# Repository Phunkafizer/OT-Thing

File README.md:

# OTthing

**A compact WiFi <-> OpenTherm (master & slave) interface**

## Project homepage

https://www.seegel-systeme.de/2025/01/05/ot-thing-das-universelle-wifi-opentherm-interface/

*OTthing board*

*OTthing wiring*

*OTthing web interface*

*Home Assistant integration*

## Overview

OTthing is a versatile OpenTherm gateway that connects your heating system to the Internet via WiFi. It acts as an OpenTherm master (controlling your boiler) and/or slave (integrating with room thermostats), providing real-time monitoring and control through a modern web interface and Home Assistant integration.

### Key Features

* **Dual OpenTherm Modes**: Operate as both an OpenTherm master and a slave simultaneously
* **Single-Board Compact Design**: Cost-efficient SMD-based single-board hardware with a small enclosure footprint
* **OpenTherm Compatibility**: Works with OpenTherm-compatible equipment that implements the functions supported by OTthing; available features vary by device
* **USB-C Powered**: Simple and reliable power supply through a standard USB-C connector
* **Web Dashboard**: Real-time status monitoring with system metrics
* **Home Assistant Integration**: Native MQTT discovery and seamless HA integration
* **Multi-Zone Support**: Control up to 2 heating circuits with independent parameters
* **Time Program**: Built-in scheduling for automatic heating setpoint changes
* **Heating Curve Control**: Outdoor-compensated flow temperature control with configurable curve parameters
* **Flow & Setpoint Management**: Fine-grained control for CH temperature targets, modes, and operating limits
* **Raw OpenTherm Tools**: Direct read/write request endpoint for diagnostics and advanced integrations
* **Real-Time Telemetry**: Live updates via WebSocket for logs and status changes
* **REST API**: Full HTTP interface for status, configuration, control commands, and topic discovery
* **WiFi Provisioning**: Built-in network scan and credential setup through the web interface
* **OTA Firmware Update**: In-browser firmware upload endpoint with automatic reboot on success
* **Local Data Export**: Device data and diagnostics export from the web UI for troubleshooting
* **External Inputs & Sensors**: Optional DS18B20, pulse input, or photointerrupter support (for example, condensate monitoring)
* **Selectable Operating Strategies**: Run OTthing as a full heating controller or in monitoring-first mode for telemetry-only operation
* **Automatic Bypass Behavior**: Allows you to restore conventional room-thermostat operation without rewiring
* **Failsafe Runtime Status**: Device health and communication state tracking for robust operation
* **Local Control**: Responsive web UI with no cloud dependency
* **Modular Design**: Extensible architecture supporting multiple integrations
* **Open-Source Platform**: Open hardware and firmware for custom extensions and modifications
* **Advanced Configuration**: Room modes (off/heat/auto), flow control, heating curves, and more
* **Detailed Logging**: Real-time log streaming to monitor system behavior
* **Turbo Mode**: Temporarily raises the flow target by a configurable amount and duration
* **Automatic Suspend**: Optional suspension based on outside temperature, room conditions, and minimum flow thresholds
* **Customizable dashboard**: add metrics to dashboard

## Architecture

The firmware consists of several functional modules:

* **OpenTherm Control** (`otcontrol.cpp`): Manages master/slave communication with the boiler
* **Master Requests** (`masterrequests.cpp`): Builds and schedules OpenTherm master requests and polling cycles
* **OpenTherm Values** (`otvalues.cpp`): Stores, normalizes, and exposes decoded OpenTherm data points
* **Heating Curve** (`heatingcurve.cpp`): Calculates the target flow temperature from heating-curve parameters
* **MQTT Integration** (`mqtt.cpp`): Publishes device state and subscribes to control topics
* **Device Status** (`devstatus.cpp`): Tracks runtime health, connectivity, and status flags
* **Auxiliary Input** (`auxInput.cpp`): Handles external input signals for additional control logic
* **Web Portal** (`portal.cpp`): Serves the responsive dashboard and API endpoints
* **Heating Control** (`CHcontrol.cpp`): Manages heating circuits, setpoints, and modes
* **Sensor Integration** (`sensors.cpp`): Collects data from external sensors
* **Configuration Management** (`devconfig.cpp`): Handles persistent device settings

## Hardware

* **MCU**: ESP32-C3 (or a compatible MCU with UART pins)
* **Communication**: OpenTherm interface
* **Power**: via USB
* **Optional**: DS18B20 1-Wire temperature sensors and auxiliary inputs

OpenTherm support and available controls depend on the boiler or other equipment. Check the device documentation and OTthing schematics before installation. Disconnect equipment from mains power before wiring; have boiler wiring performed by a qualified installer where required. Connect OpenTherm through the board's designated terminals, never directly to MCU GPIO pins.

## Installation & Setup

1. **Hardware Setup**:

   - Connect the OpenTherm slave side (boiler / ventilation / solar storage) to the **Boiler** screw terminal on OTthing
   - Optionally connect the room unit to the **Roomunit** screw terminals on OTthing
   - Connect OTthing to a USB-C power supply

2. **Access the Web Interface**:

   - The device creates a WiFi access point for provisioning or connects to its configured network
   - The default access point password is `12345678`; change it before deployment
   - Access the web UI at `http://<otthing-ip>/` (default: 4.3.2.1)

3. **Configure**:

   - Set your boiler type and heating circuit parameters
   - Configure the MQTT broker if you are using Home Assistant
   - Adjust setpoints, heating curves, and control modes

### Build and Flash (Developers)

Install PlatformIO, then run these commands from the `Firmware/` directory:

```bash
platformio run --environment release
platformio run --environment release --target upload
```

The first command builds the firmware. The next two upload the firmware and the LittleFS web assets; perform both uploads when installing a complete build. The firmware project reads access point SSID, password, and hostname from `default.ini` unless overridden by the build environment. Set a unique access point password before deploying devices.

## API Reference

OTthing exposes the following REST endpoints and WebSocket connection:

When web authentication is configured, protected endpoints require a valid login session. Requests without a valid session return 401; log in through the web UI before using these endpoints.

### Core Status Endpoints

* **`GET /`** - Web dashboard (HTML)
* **`GET /status`** - Current device and boiler status (JSON)
* **`GET /config`** - Device configuration and settings (JSON)
* **`POST /config`** - Update device configuration (JSON body)
* **`GET /otitems`** - Raw OpenTherm items and values from master and slave (JSON)
* **`GET /topics`** - List all available MQTT control topics (text/plain)

### Control Endpoints

* **`GET /set?key=value`** - Update settings via query parameters
  - Examples: `/set?chSetTemp1=50`, `/set?chMode1=heat`
  - Use `/topics` to discover supported control keys. URL-encode values when they contain reserved characters.
  - Returns 200 on success, 503 if the value cannot be set

* **`GET /slaverequest?id=X&rw=Y&data=HEX`** - Send a raw OpenTherm slave request
  - `id`: OpenTherm message ID (integer)
  - `rw`: 1 for READ_DATA, 0 for WRITE_DATA
  - `data`: Hex-encoded data value
  - Returns JSON with response type, ID, and data

### System Endpoints

* **`GET /scan`** - Scan for available WiFi networks
  - Returns JSON with the SSID, RSSI, and channel for each network
  - Status field: -2 (scanning in progress), -1 (failed), 0+ (number of networks found)

* **`POST /setwifi`** - Configure WiFi credentials
  - Parameters: `ssid` and `pass` (URL-encoded)
  - Triggers a device reboot and a WiFi connection attempt

* **`GET /reboot`** - Trigger a device reboot
  - Returns 200 and schedules a reboot

* **`POST /update`** - Firmware update (binary upload)
  - Returns 200 on success, 500/503 on error
  - Triggers an automatic reboot if the update succeeds

### Real-time Communication

* **`WebSocket /ws`** - Real-time updates and log streaming
  - Receives log messages and status updates
  - Can be used to monitor device behavior in real time

## Testing & Development

A Python mock server is included for local UI and API testing. Install its dependencies and start it from the `Firmware/` directory:

```bash
python -m pip install -r requirements.txt
python tools/mock_otthing.py
```

The server listens on `http://127.0.0.1:8081/`. It is useful for UI development and API integration, but it does not replace testing against physical OpenTherm hardware.

### MQTT Notes

The device subscribes to control topics under `otthing/<device-id>/<key>/set`; `/topics` lists the supported keys. Home Assistant discovery is provided through MQTT when a broker is configured.

Changes sent through the web API are also published to the corresponding MQTT `/set` topic as retained messages. A broker can replay retained commands when the device reconnects, including after a reboot. Keep this in mind for temporary controls such as Turbo mode, and clear any stale retained command from the broker when needed.

### Troubleshooting

* **Cannot reach the web UI**: Confirm the phone or computer is connected to the OTthing access point or the same network as the device, then check the device IP.
* **No OpenTherm communication**: Check the board terminals, wiring polarity where applicable, boiler compatibility, and the device's status and logs.
* **Home Assistant entities are missing**: Confirm broker connectivity and MQTT discovery settings, then review device logs and the broker's topics.
* **A setting returns 401**: Log in through the web UI and retry the request with the browser session.
* **A temporary action returns after reboot**: Check whether a retained MQTT `/set` command is replaying it.

## Schematics

## Discussion

https://community.home-assistant.io/t/ot-thing-an-opentherm-wifi-gateway-with-integrated-ot-master-slave/824667

## Reporting issues

When reporting issues, please supply:

* Brand and model of the boiler and room unit
* OTthing firmware version and the steps that reproduce the issue
* expected behaviour
* Log
* Status JSON
* Configuration JSON
* OT items JSON
* Data history JSON

All of this data can be exported from the OTthing using the export function at the bottom of the web UI.
Only one concern per issue!

## Contributing

* Make changes in a new branch based on the [`develop`](../../tree/develop) branch.
* Address only one issue per PR.
* Create the PR against the [`develop`](../../tree/develop) branch.

## Known Working Devices

Below is an excerpt of hardware devices reported to work successfully with **OTthing**. If you have verified additional devices, contributions and reports are very welcome!

### Boilers & Heating Systems
* **De Dietrich** Inidens 20/24 MI
* **De Dietrich** MCR 24 Home
* **De Dietrich** MPX 24/29 MI Compact
* **Domusa** BioClass HM 16 (Pellet)
* **Hoval** TopGas
* **Intergas** Xtreme 36
* **Intergas** HRE 36/30A
* **Junkers** Cerasmart ZSB 3-16 *(with OpenTherm module OTM 1)*
* **Remeha** Tzerra 28c
* **Remeha** Tzerra Ace
* **Termet** Gold Plus 2
* **Viessmann** Vitodens 100-W (B1KG)
* **Westen** Boyler Digit+
* **Windhager** BioWin (Pellet)

### Room Units & Thermostats
* **Baxi** RC 06.20
* **De Dietrich** AD304
* **De Dietrich** iSense (AD289)
* **Honeywell** DT4M
* **Hoval** RS-OT
* **Junkers** TF 30
* **Siemens** QAA73
* **Theben / Windhager** RAM 786

---
*Feel free to open a Pull Request or issue to report additional compatible devices!*

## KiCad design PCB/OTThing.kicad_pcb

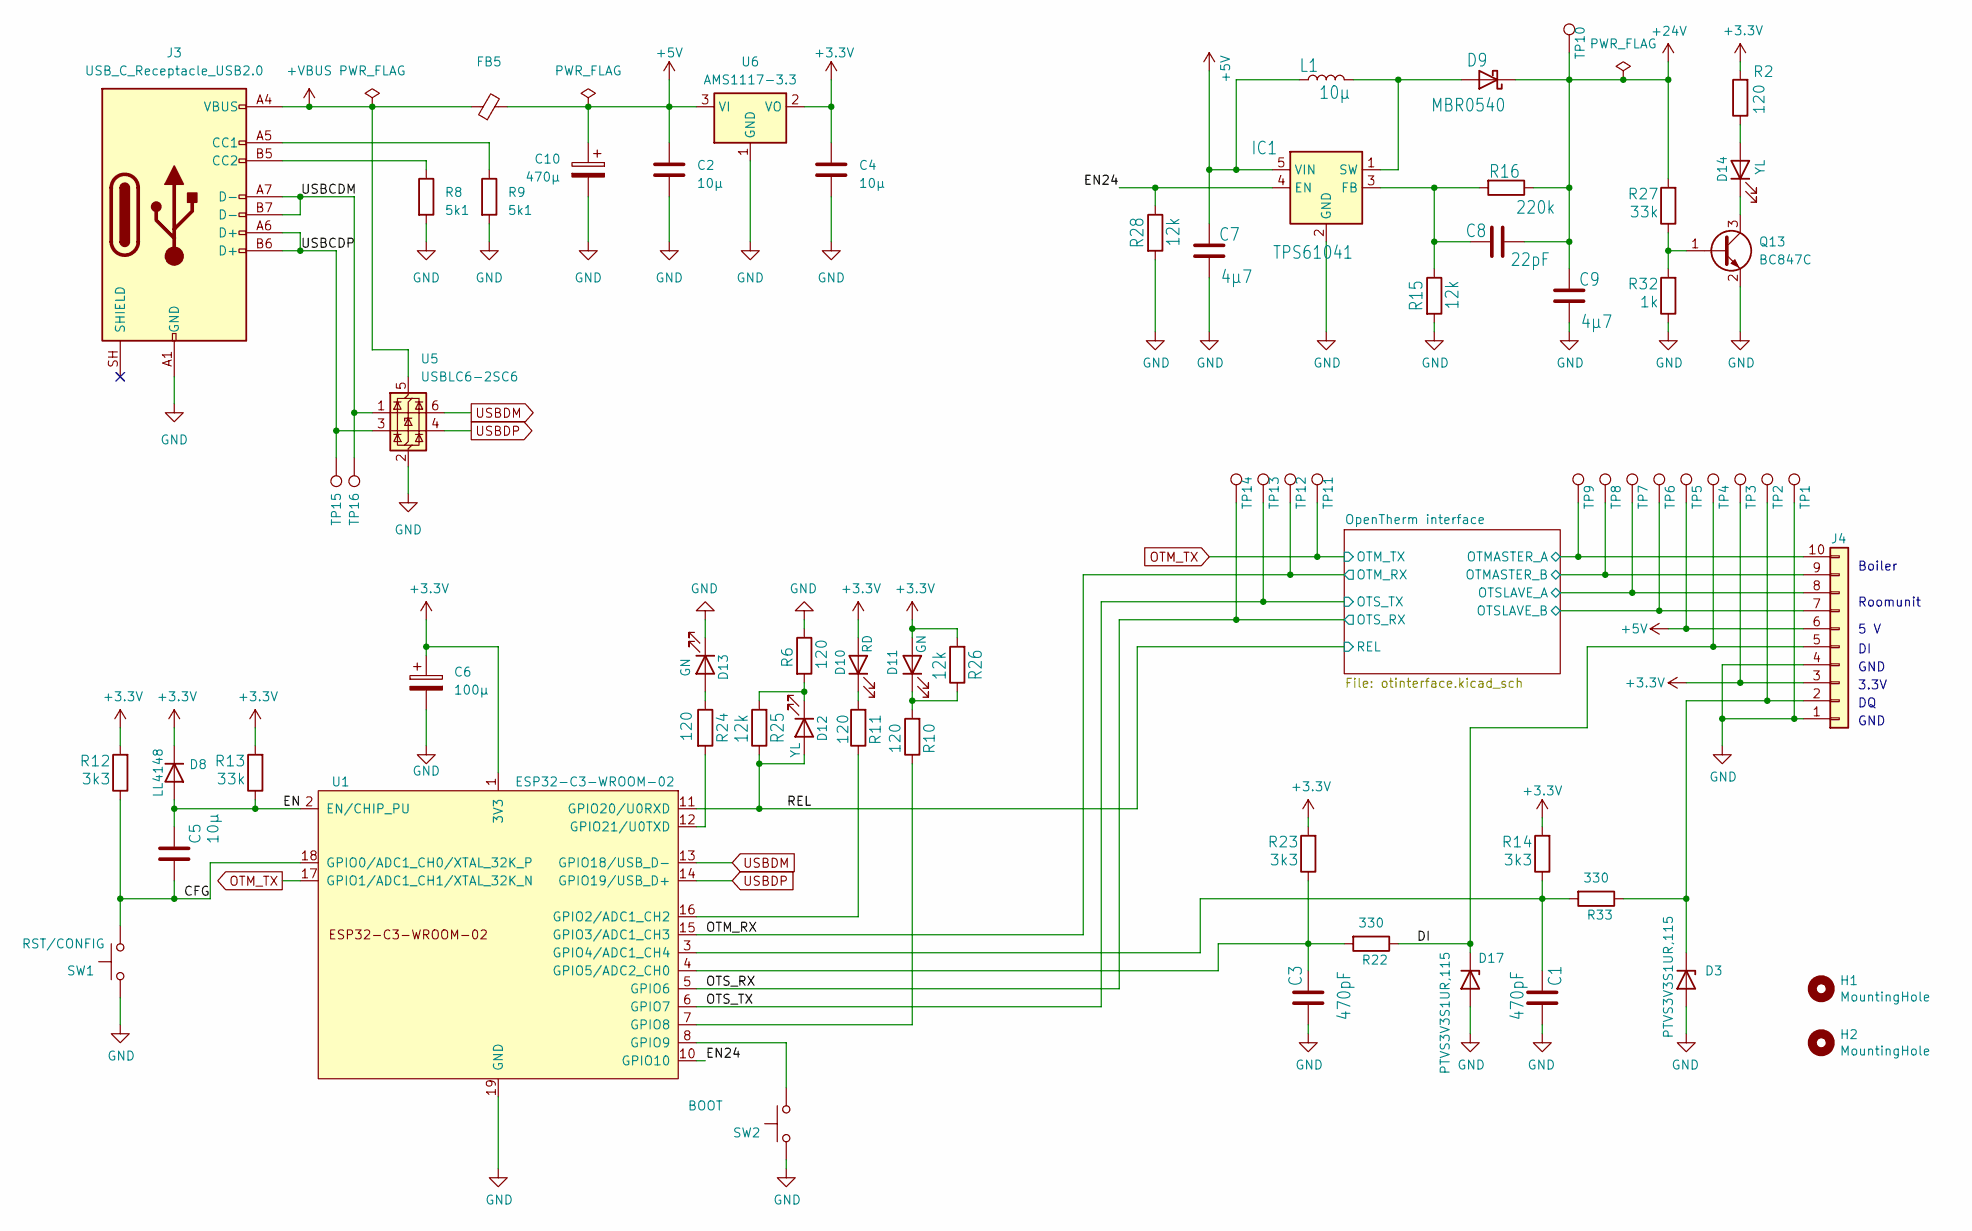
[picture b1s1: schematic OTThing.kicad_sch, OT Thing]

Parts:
C1, C3: 470pF; C_0805_2012Metric; LCSC C62771
C2, C4, C5: 10µ; C_0805_2012Metric; LCSC C90543
C6: 100µ; CP_Elec_6.3x5.4; LCSC C2887276
C7, C9: 4µ7; C_0805_2012Metric; LCSC C2918489
C8: 22pF; C_0805_2012Metric; LCSC C24658
C10: 470µ; CP_Elec_6.3x7.7; LCSC C87858
D3, D17: PTVS3V3S1UR,115; D_SOD-123; LCSC C183521
D8: LL4148; D_MiniMELF; LCSC C435829
D9: MBR0540; D_SOD-123; LCSC C116159
D10: RD; LED_0805_2012Metric; LCSC C2943978
D11, D13: GN; LED_0805_2012Metric; LCSC C965815
D12, D14: YL; LED_0805_2012Metric; LCSC C965816
FB5: L_0603_1608Metric; LCSC C1002
H1, H2: MountingHole; MountingHole_2.5mm
IC1: TPS61041; SOT-23-5; LCSC C9846
J3: USB_C_Receptacle_USB2.0; USB_C_Receptacle_HRO_TYPE-C-31-M-12; LCSC C2927038
J4: TerminalBlock_Phoenix_PT-1,5-10-3.5-H_1x10_P3.50mm_Horizont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; LCSC C5184956
L1: 10µ; L_1210_3225Metric; LCSC C98020
Q13: BC847C; SOT-23; LCSC C7420337
R2, R6, R10, R11, R24: 120; R_0805_2012Metric; LCSC C17437
R8, R9: 5k1; R_0805_2012Metric; LCSC C118848
R12, R14, R23: 3k3; R_0805_2012Metric; LCSC C26010
R13, R27: 33k; R_0805_2012Metric; LCSC C17633
R15, R25, R26, R28: 12k; R_0805_2012Metric; LCSC C17444
R16: 220k; R_0805_2012Metric; LCSC C17556
R22, R33: 330; R_0805_2012Metric; LCSC C17630
R32: 1k; R_0805_2012Metric; LCSC C17513
SW1: RST/CONFIG; SW_Tactile_SPST_Angled_PTS645Vx83-2LFS; LCSC C2837540
SW2: BOOT; SW_SPST_CK_RS282G05A3; LCSC C2888954
TP1, TP2, TP3, TP4, TP5, TP6, TP7, TP8, TP9, TP10, TP11, TP12, TP13, TP14, TP15, TP16: TestPoint_THTPad_D1.5mm_Drill0.7mm
U1: ESP32-C3-WROOM-02; LCSC C2934560
U5: USBLC6-2SC6; SOT-23-6; LCSC C2827654
U6: AMS1117-3.3; SOT-223-3_TabPin2; LCSC C347222

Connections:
+3.3V: C4.1, C6.1, D8.1 (K), D10.2 (A), D11.2 (A), J4.3, R2.2, R12.2, R13.2, R14.2, R23.2, R26.2, TP3.1 (1_1), U1.1 (3V3), U6.2 (VO); also elsewhere on the board
+5V: C2.1, C7.1, C10.1, FB5.2, IC1.5 (VIN), J4.6, L1.1, TP5.1 (1_1), U6.3 (VI); also elsewhere on the board
+24V: C8.1, C9.1, D9.1 (K), R16.1, R27.2, TP10.1 (1_1); also elsewhere on the board
+VBUS: FB5.1, J3.A4 (VBUS), J3.A9 (VBUS), J3.B4 (VBUS), J3.B9 (VBUS), U5.5 (VBUS)
/CFG: C5.2, R12.1, SW1.1, U1.18 (GPIO0/ADC1_CH0/XTAL_32K_P)
/DI: D17.1 (K), J4.5, R22.1, TP4.1 (1_1)
/EN: C5.1, D8.2 (A), R13.1, U1.2 (EN/CHIP_PU)
/EN24: IC1.4 (EN), R28.1, U1.10 (GPIO10)
/OTM_RX: TP12.1 (1_1), U1.15 (GPIO3/ADC1_CH3); also elsewhere on the board
/OTS_RX: TP14.1 (1_1), U1.5 (GPIO6); also elsewhere on the board
/OTS_TX: TP13.1 (1_1), U1.6 (GPIO7); also elsewhere on the board
/OpenTherm interface/OTMASTER_A: J4.10, TP9.1 (1_1); also elsewhere on the board
/OpenTherm interface/OTMASTER_B: J4.9, TP8.1 (1_1); also elsewhere on the board
/OpenTherm interface/OTSLAVE_A: J4.8, TP7.1 (1_1); also elsewhere on the board
/OpenTherm interface/OTSLAVE_B: J4.7, TP6.1 (1_1); also elsewhere on the board
/REL: D12.2 (A), R25.1, U1.11 (GPIO20/U0RXD); also elsewhere on the board
/USBCDM: J3.A7 (D-), J3.B7 (D-), TP16.1 (1_1), U5.1 (I/O1)
/USBCDP: J3.A6 (D+), J3.B6 (D+), TP15.1 (1_1), U5.3 (I/O2)
GND: C1.2, C2.2, C3.2, C4.2, C6.2, C7.2, C9.2, C10.2, D3.2 (A), D13.1 (K), D17.2 (A), IC1.2 (GND), J3.A1 (GND), J3.A12 (GND), J3.B1 (GND), J3.B12 (GND), J4.1, J4.4, Q13.2 (E), R6.1, R8.2, R9.2, R15.2, R28.2, R32.1, SW1.2, SW2.2, TP1.1 (1_1), U1.9 (GND), U1.19 (GND), U5.2 (GND), U6.1 (GND); also elsewhere on the board
unnamed: D3.1 (K), J4.2, R33.1, TP2.1 (1_1)
unnamed: D9.2 (A), IC1.1 (SW), L1.2
unnamed: D10.1 (K), R11.2
unnamed: D11.1 (K), R10.2, R26.1
unnamed: D12.1 (K), R6.2, R25.2
unnamed: D13.2 (A), R24.1
unnamed: D14.2 (A), R2.1
unnamed: D14.1 (K), Q13.3 (C)
unnamed: C8.2, IC1.3 (FB), R15.1, R16.2
unnamed: J3.A5 (CC1), R9.1
unnamed: J3.B5 (CC2), R8.1
unnamed: Q13.1 (B), R27.1, R32.2
unnamed: R11.1, U1.16 (GPIO2/ADC1_CH2)
unnamed: C1.1, R14.1, R33.2, U1.3 (GPIO4/ADC1_CH4)
unnamed: C3.1, R22.2, R23.1, U1.4 (GPIO5/ADC2_CH0)
unnamed: R10.1, U1.7 (GPIO8)
unnamed: SW2.1, U1.8 (GPIO9)
unnamed: R24.2, U1.12 (GPIO21/U0TXD)
OTM_TX: TP11.1 (1_1), U1.17 (GPIO1/ADC1_CH1/XTAL_32K_N); also elsewhere on the board
USBDM: U1.13 (GPIO18/USB_D-), U5.6 (I/O1)
USBDP: U1.14 (GPIO19/USB_D+), U5.4 (I/O2)

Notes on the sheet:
Boiler
3.3V
GND
5 V
Roomunit

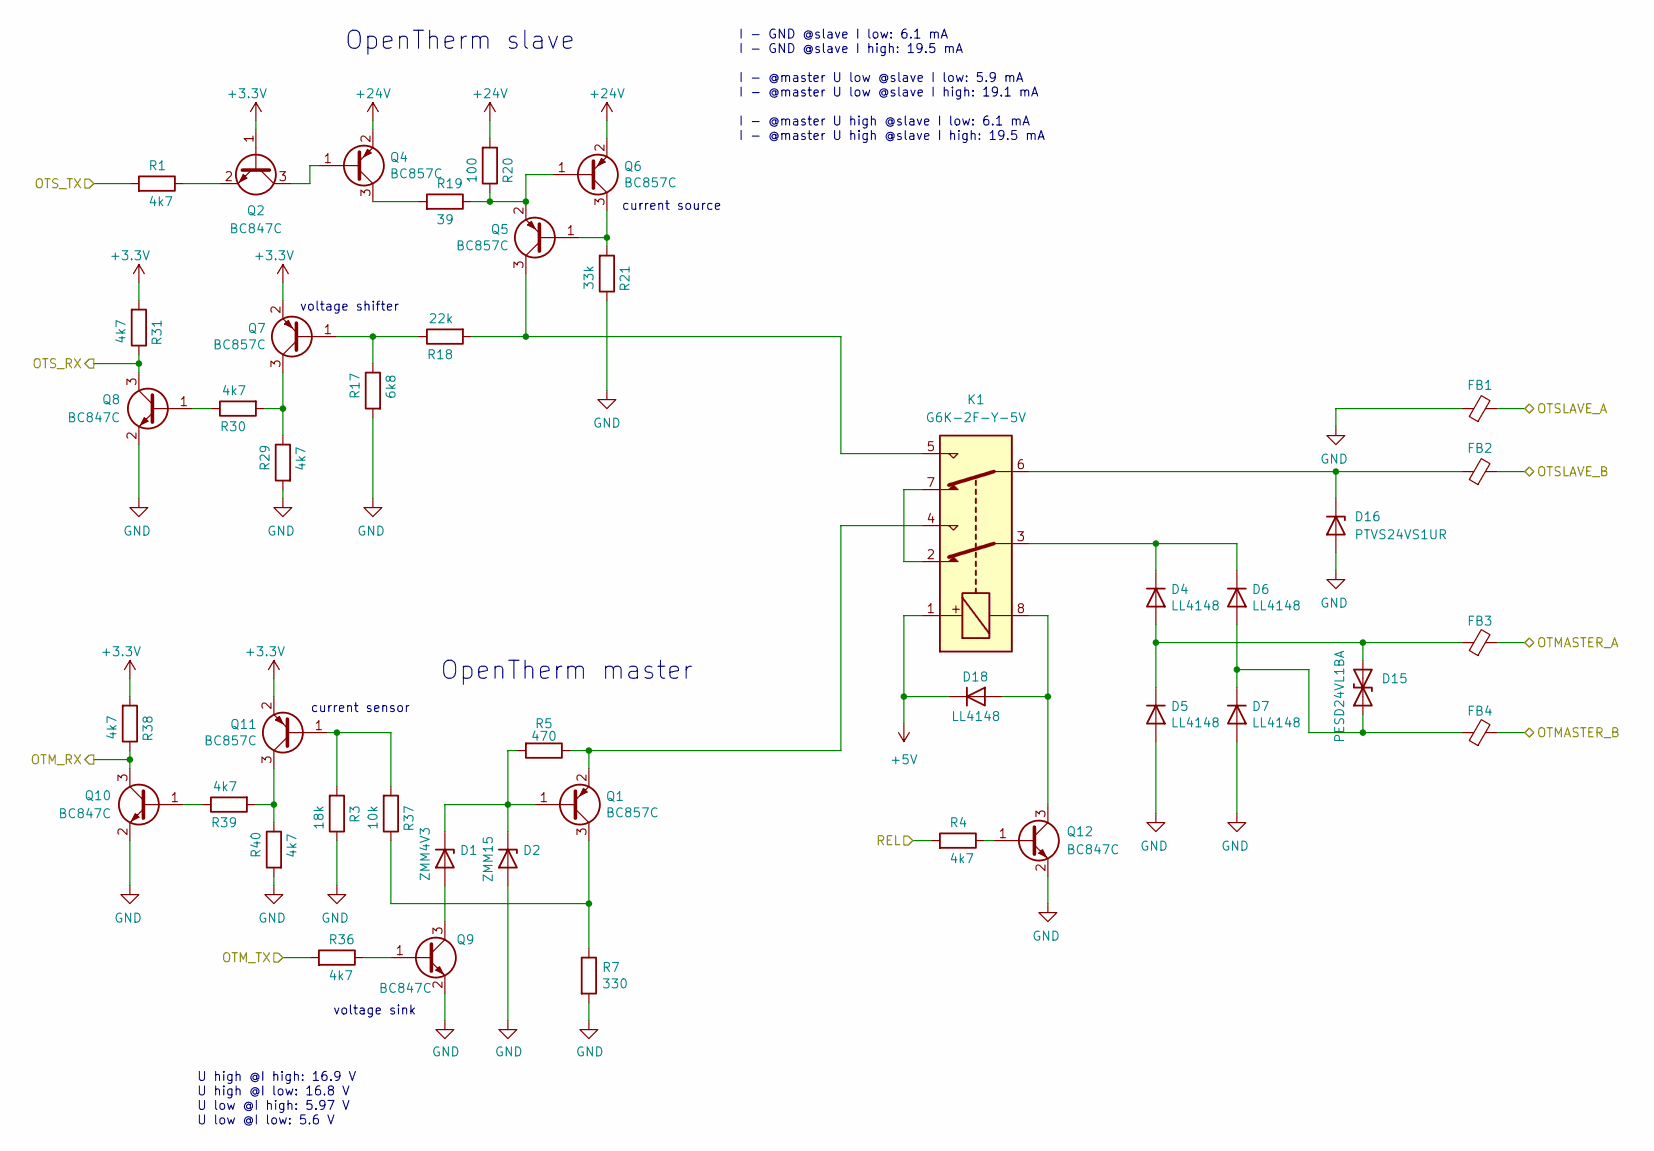
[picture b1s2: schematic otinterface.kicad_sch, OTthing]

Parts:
D1: ZMM4V3; D_MiniMELF; LCSC C5345990
D2: ZMM15; D_MiniMELF; LCSC C5346000
D4, D5, D6, D7, D18: LL4148; D_MiniMELF; LCSC C435829
D15: PESD24VL1BA; D_SOD-323; LCSC C2687132
D16: PTVS24VS1UR; D_SOD-123; LCSC C5380693
FB1, FB2, FB3, FB4: L_0603_1608Metric; LCSC C1002
K1: G6K-2F-Y-5V; Relay_DPDT_Omron_G6K-2F-Y; LCSC C2982926
Q1, Q4, Q5, Q6, Q7, Q11: BC857C; SOT-23; LCSC C5204725
Q2, Q8, Q9, Q10, Q12: BC847C; SOT-23; LCSC C7420337
R1, R4, R29, R30, R31, R36, R38, R39, R40: 4k7; R_0805_2012Metric; LCSC C17673
R3: 18k; R_0805_2012Metric; LCSC C17506
R5: 470; R_0805_2012Metric; LCSC C17710
R7: 330; R_0805_2012Metric; LCSC C17630
R17: 6k8; R_0805_2012Metric; LCSC C17772
R18: 22k; R_0805_2012Metric; LCSC C17560
R19: 39; R_0805_2012Metric; LCSC C137534
R20: 100; R_0805_2012Metric; LCSC C17408
R21: 33k; R_0805_2012Metric; LCSC C17633
R37: 10k; R_0805_2012Metric; LCSC C17414

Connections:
+3.3V: Q2.1 (B), Q7.2 (E), Q11.2 (E), R31.2, R38.2; also elsewhere on the board
+5V: D18.1 (K), K1.1; also elsewhere on the board
+24V: Q4.2 (E), Q6.2 (E), R20.2; also elsewhere on the board
/OTM_RX: Q10.3 (C), R38.1; also elsewhere on the board
/OTS_RX: Q8.3 (C), R31.1; also elsewhere on the board
/OTS_TX: R1.2; also elsewhere on the board
/OpenTherm interface/OTMASTER_A: FB3.2; also elsewhere on the board
/OpenTherm interface/OTMASTER_B: FB4.2; also elsewhere on the board
/OpenTherm interface/OTSLAVE_A: FB1.2; also elsewhere on the board
/OpenTherm interface/OTSLAVE_B: FB2.2; also elsewhere on the board
/REL: R4.2; also elsewhere on the board
GND: D2.2 (A), D5.2 (A), D7.2 (A), D16.2 (A), FB1.1, Q8.2 (E), Q9.2 (E), Q10.2 (E), Q12.2 (E), R3.1, R7.2, R17.2, R21.1, R29.2, R40.2; also elsewhere on the board
unnamed: D1.2 (A), Q9.3 (C)
unnamed: D1.1 (K), D2.1 (K), Q1.1 (B), R5.2
unnamed: D4.1 (K), D6.1 (K), K1.3
unnamed: D6.2 (A), D7.1 (K), D15.1 (A1), FB4.1
unnamed: D4.2 (A), D5.1 (K), D15.2 (A2), FB3.1
unnamed: D16.1 (K), FB2.1, K1.6
unnamed: D18.2 (A), K1.8, Q12.3 (C)
unnamed: K1.2, K1.7
unnamed: Q1.3 (C), R7.1, R37.1
unnamed: K1.4, Q1.2 (E), R5.1
unnamed: Q2.3 (C), Q4.1 (B)
unnamed: Q2.2 (E), R1.1
unnamed: Q4.3 (C), R19.2
unnamed: Q5.1 (B), Q6.3 (C), R21.2
unnamed: K1.5, Q5.3 (C), R18.2
unnamed: Q5.2 (E), Q6.1 (B), R19.1, R20.1
unnamed: Q7.1 (B), R17.1, R18.1
unnamed: Q7.3 (C), R29.1, R30.2
unnamed: Q8.1 (B), R30.1
unnamed: Q9.1 (B), R36.1
unnamed: Q10.1 (B), R39.1
unnamed: Q11.1 (B), R3.2, R37.2
unnamed: Q11.3 (C), R39.2, R40.1
unnamed: Q12.1 (B), R4.1
OTM_TX: R36.2; also elsewhere on the board

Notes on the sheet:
current sensor
current source
U high @I high: 16.9 V U high @I low: 16.8 V U low @I high: 5.97 V U low @I low: 5.6 V
I - GND @slave I low: 6.1 mA I - GND @slave I high: 19.5 mA I - @master U low @slave I low: 5.9 mA I - @master U low @slave I high: 19.1 mA I - @master U high @slave I low: 6.1 mA I - @master U high @slave I high: 19.5 mA
voltage shifter
OpenTherm slave
OpenTherm master
voltage sink

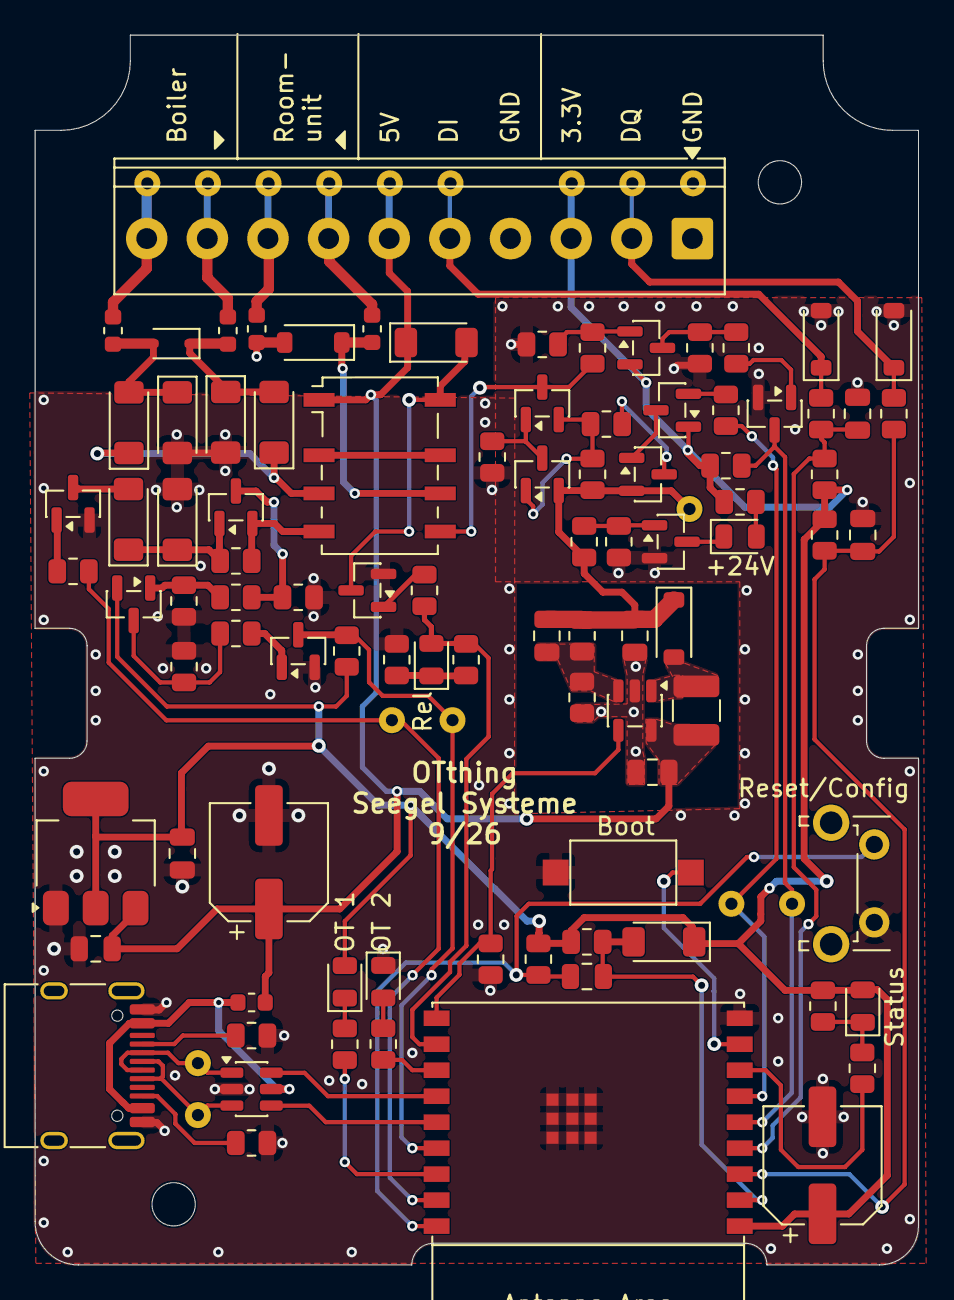
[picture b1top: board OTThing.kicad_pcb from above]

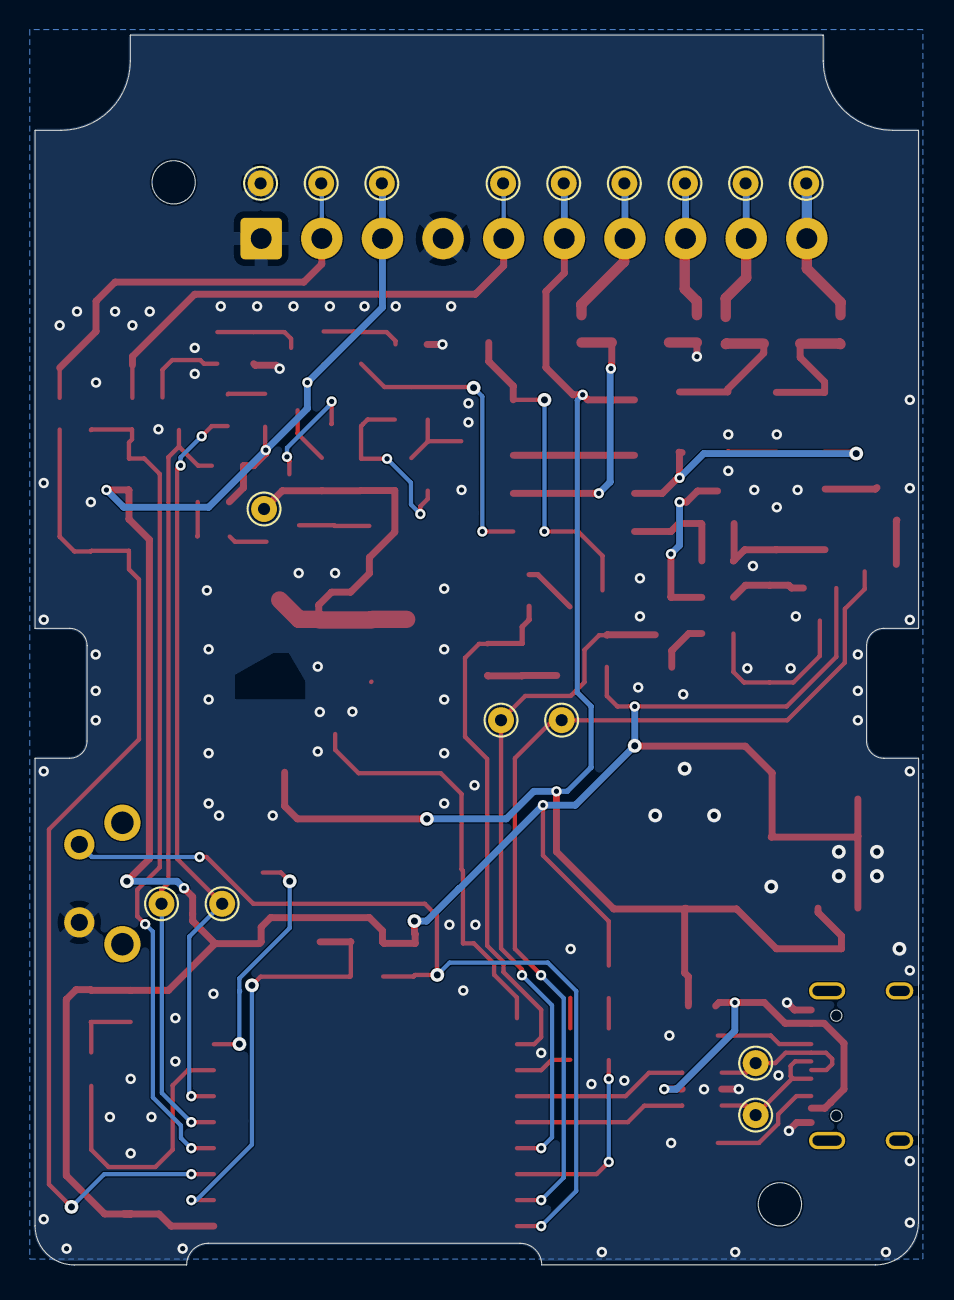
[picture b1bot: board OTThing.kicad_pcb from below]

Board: 2 copper layers, 51.0 x 71.0 mm, 111 parts (16 on the bottom side), 64 nets.

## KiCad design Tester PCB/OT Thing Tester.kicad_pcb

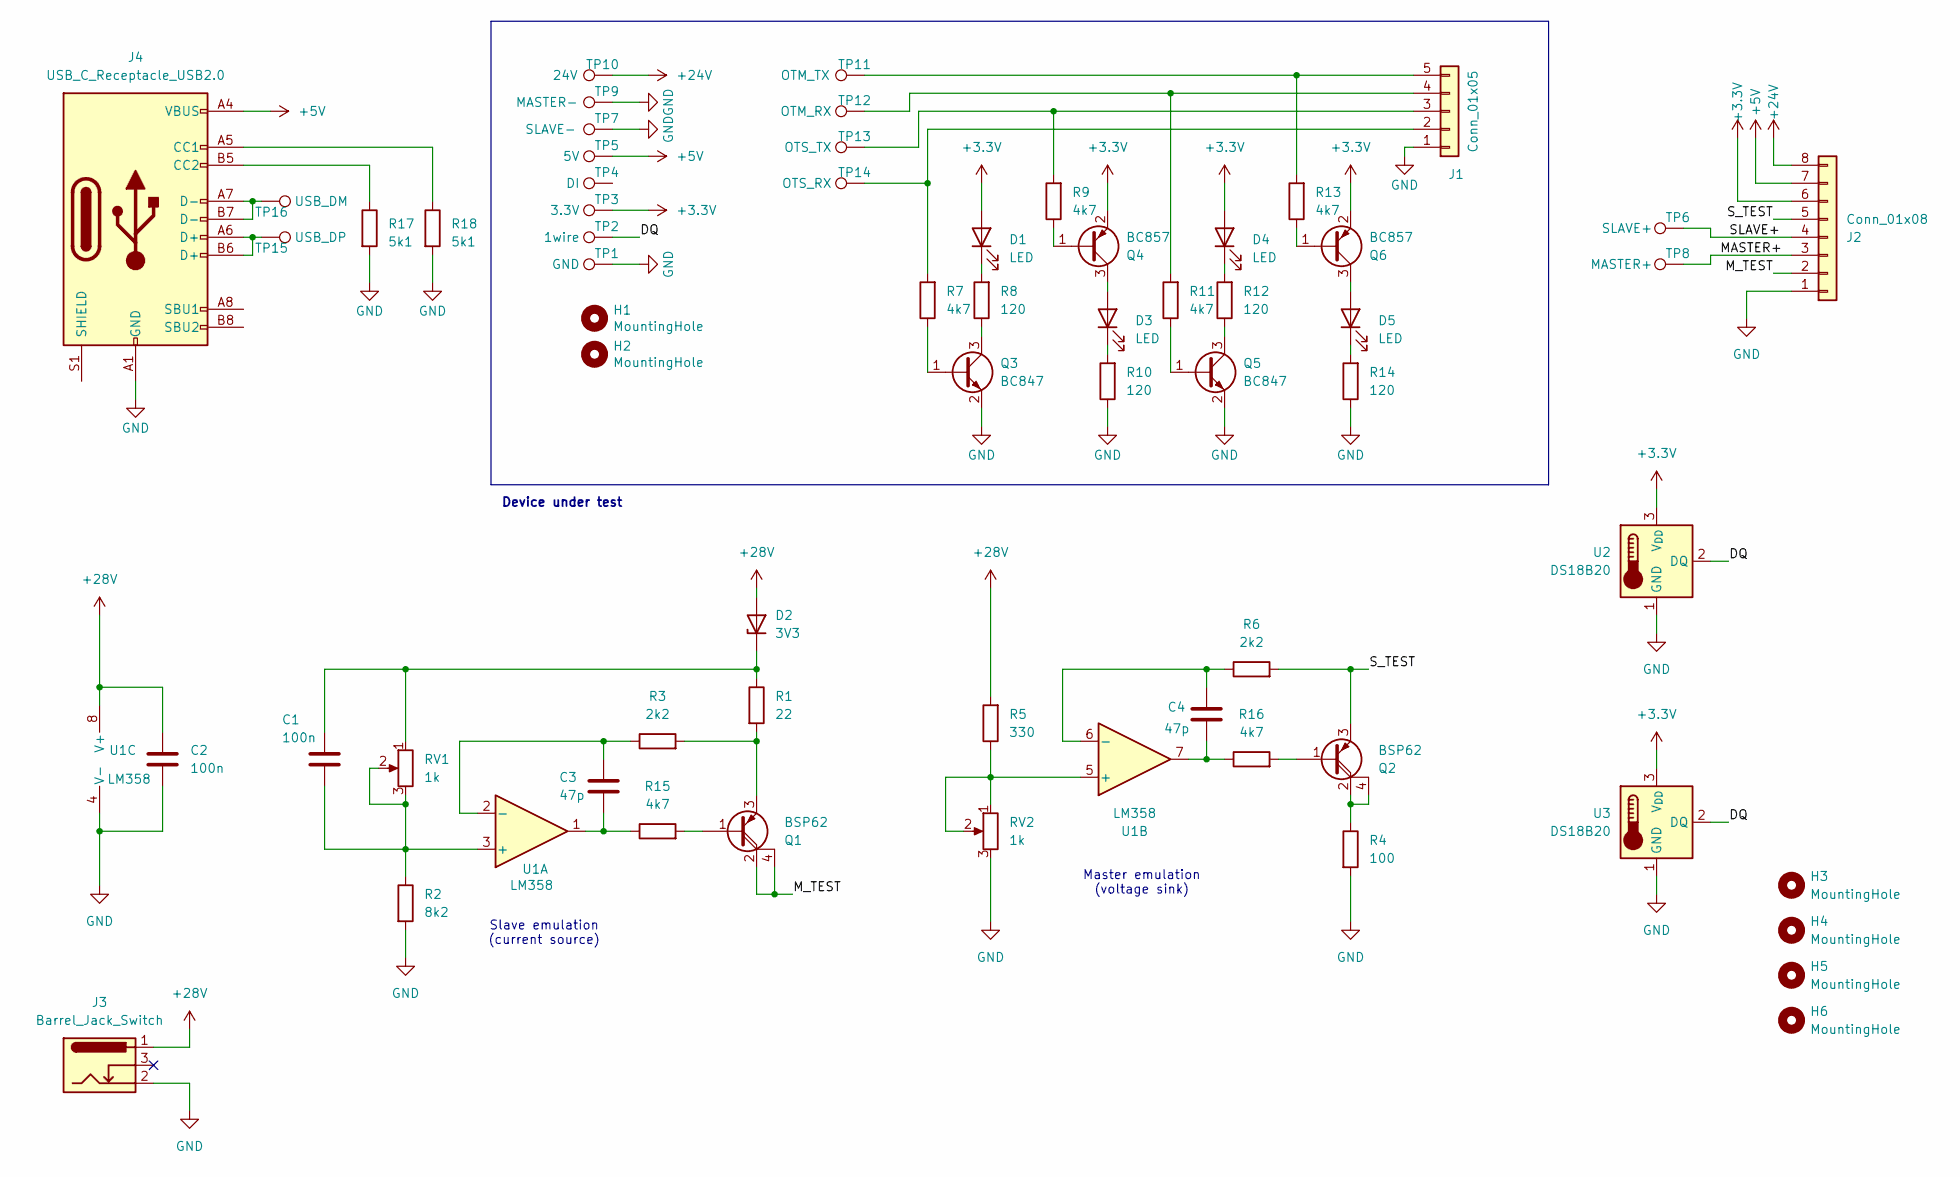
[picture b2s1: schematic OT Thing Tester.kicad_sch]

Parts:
C1, C2: 100n; C_0805_2012Metric
C3, C4: 47p; C_0805_2012Metric
D1, D3, D4, D5: LED; LED_0805_2012Metric
D2: 3V3; D_MiniMELF
H1, H2: MountingHole; MountingHole_2.7mm_M2.5
H3, H4, H5, H6: MountingHole; MountingHole_3.2mm_M3_DIN965_Pad
J1: Conn_01x05; PinHeader_1x05_P2.54mm_Vertical
J2: Conn_01x08; PinHeader_1x08_P2.54mm_Vertical
J3: Barrel_Jack_Switch; BarrelJack_GCT_DCJ200-10-A_Horizontal
J4: USB_C_Receptacle_USB2.0; USB_C_Receptacle_HRO_TYPE-C-31-M-12; LCSC C2927038
Q1, Q2: BSP62; SOT-223
Q3, Q5: BC847; SOT-23
Q4, Q6: BC857; SOT-23
R1: 22; R_0805_2012Metric
R2: 8k2; R_0805_2012Metric
R3, R6: 2k2; R_0805_2012Metric
R4: 100; R_0805_2012Metric
R5: 330; R_0805_2012Metric
R7, R9, R11, R13, R15, R16: 4k7; R_0805_2012Metric
R8, R10, R12, R14: 120; R_0805_2012Metric
R17, R18: 5k1; R_0805_2012Metric; LCSC C118848
RV1, RV2: 1k; Potentiometer_Piher_PT-6-V_Vertical
TP1: GND; TestPoint_THTPad_D2.0mm_Drill1.1mm
TP2: 1wire; TestPoint_THTPad_D2.0mm_Drill1.1mm
TP3: 3.3V; TestPoint_THTPad_D2.0mm_Drill1.1mm
TP4: DI; TestPoint_THTPad_D2.0mm_Drill1.1mm
TP5: 5V; TestPoint_THTPad_D2.0mm_Drill1.1mm
TP6: SLAVE+; TestPoint_THTPad_D2.0mm_Drill1.1mm
TP7: SLAVE-; TestPoint_THTPad_D2.0mm_Drill1.1mm
TP8: MASTER+; TestPoint_THTPad_D2.0mm_Drill1.1mm
TP9: MASTER-; TestPoint_THTPad_D2.0mm_Drill1.1mm
TP10: 24V; TestPoint_THTPad_D2.0mm_Drill1.1mm
TP11: OTM_TX; TestPoint_THTPad_D2.0mm_Drill1.1mm
TP12: OTM_RX; TestPoint_THTPad_D2.0mm_Drill1.1mm
TP13: OTS_TX; TestPoint_THTPad_D2.0mm_Drill1.1mm
TP14: OTS_RX; TestPoint_THTPad_D2.0mm_Drill1.1mm
TP15: USB_DP; TestPoint_THTPad_D2.0mm_Drill1.1mm
TP16: USB_DM; TestPoint_THTPad_D2.0mm_Drill1.1mm
U1: LM358; SO-8_3.9x4.9mm_P1.27mm
U2, U3: DS18B20; TO-92_Inline

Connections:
+3.3V: D1.2 (A), D4.2 (A), J2.6, Q4.2 (E), Q6.2 (E), TP3.1 (1_1), U2.3 (V_{DD}), U3.3 (V_{DD})
+5V: J2.7, J4.A4 (VBUS), J4.A9 (VBUS), J4.B4 (VBUS), J4.B9 (VBUS), TP5.1 (1_1)
+24V: J2.8, TP10.1 (1_1)
+28V: C2.1, D2.2 (A), J3.1, R5.2, U1.8 (V+)
/DQ: TP2.1 (1_1), U2.2 (DQ), U3.2 (DQ)
/MASTER+: J2.3, TP8.1 (1_1)
/M_TEST: J2.2, Q1.2 (C), Q1.4 (C)
/SLAVE+: J2.4, TP6.1 (1_1)
/S_TEST: J2.5, Q2.3 (E), R6.2
unnamed: C3.2, R15.1, U1.1
unnamed: C4.2, R16.1, U1.7
unnamed: D1.1 (K), R8.2
unnamed: C1.2, D2.1 (K), R1.1, RV1.1
unnamed: D3.2 (A), Q4.3 (C)
unnamed: D3.1 (K), R10.2
unnamed: D4.1 (K), R12.2
unnamed: D5.2 (A), Q6.3 (C)
unnamed: D5.1 (K), R14.2
unnamed: J1.2, R7.2, TP14.1 (1_1)
unnamed: J1.3, R9.2, TP13.1 (1_1)
unnamed: J1.4, R11.2, TP12.1 (1_1)
unnamed: J1.5, R13.2, TP11.1 (1_1)
unnamed: J4.A5 (CC1), R18.1
unnamed: J4.B5 (CC2), R17.1
unnamed: J4.A6 (D+), J4.B6 (D+), TP15.1 (1_1)
unnamed: J4.A7 (D-), J4.B7 (D-), TP16.1 (1_1)
unnamed: Q1.1 (B), R15.2
unnamed: Q1.3 (E), R1.2, R3.2
unnamed: Q2.1 (B), R16.2
unnamed: Q2.2 (C), Q2.4 (C), R4.1
unnamed: Q3.1 (B), R7.1
unnamed: Q3.3 (C), R8.1
unnamed: Q4.1 (B), R9.1
unnamed: Q5.1 (B), R11.1
unnamed: Q5.3 (C), R12.1
unnamed: Q6.1 (B), R13.1
unnamed: C1.1, R2.1, RV1.2, RV1.3, U1.3 (+)
unnamed: C3.1, R3.1, U1.2 (-)
unnamed: C4.1, R6.1, U1.6 (-)

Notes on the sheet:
Master emulation (voltage sink)
Slave emulation (current source)
Device under test

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
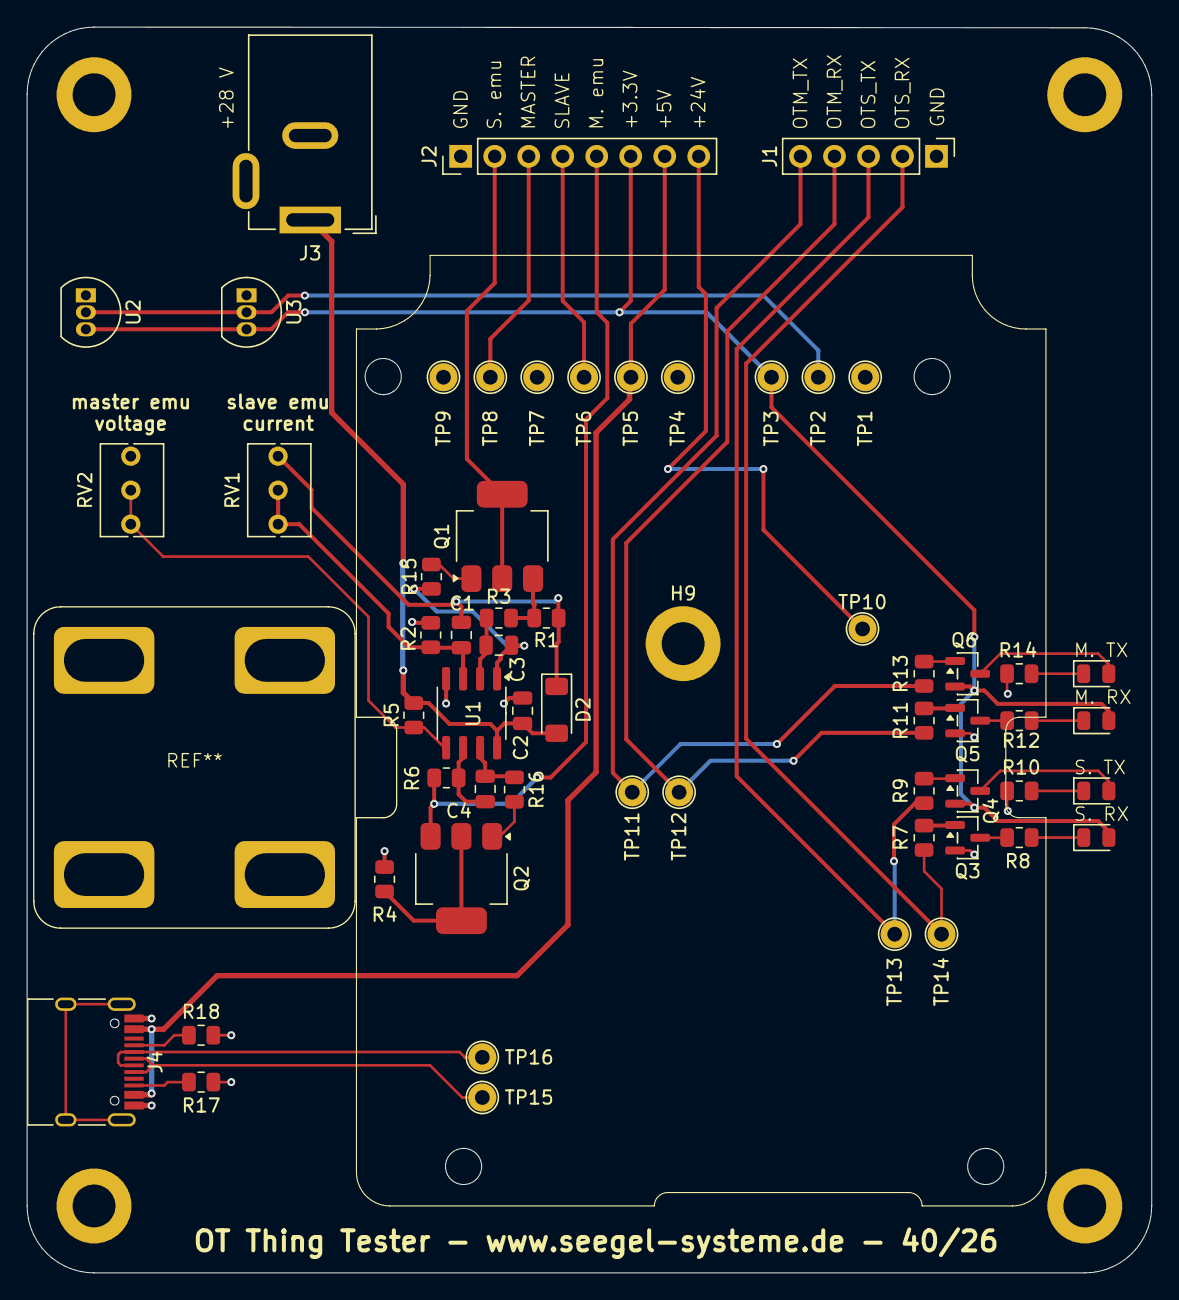
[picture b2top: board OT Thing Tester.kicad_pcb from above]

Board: 2 copper layers, 84.0 x 93.0 mm, 67 parts (0 on the bottom side), 41 nets.

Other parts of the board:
H7, H8: MountingHole; MountingHole_2.7mm_M2.5
H9: MountingHole; MountingHole_3.2mm_M3_DIN965_Pad
